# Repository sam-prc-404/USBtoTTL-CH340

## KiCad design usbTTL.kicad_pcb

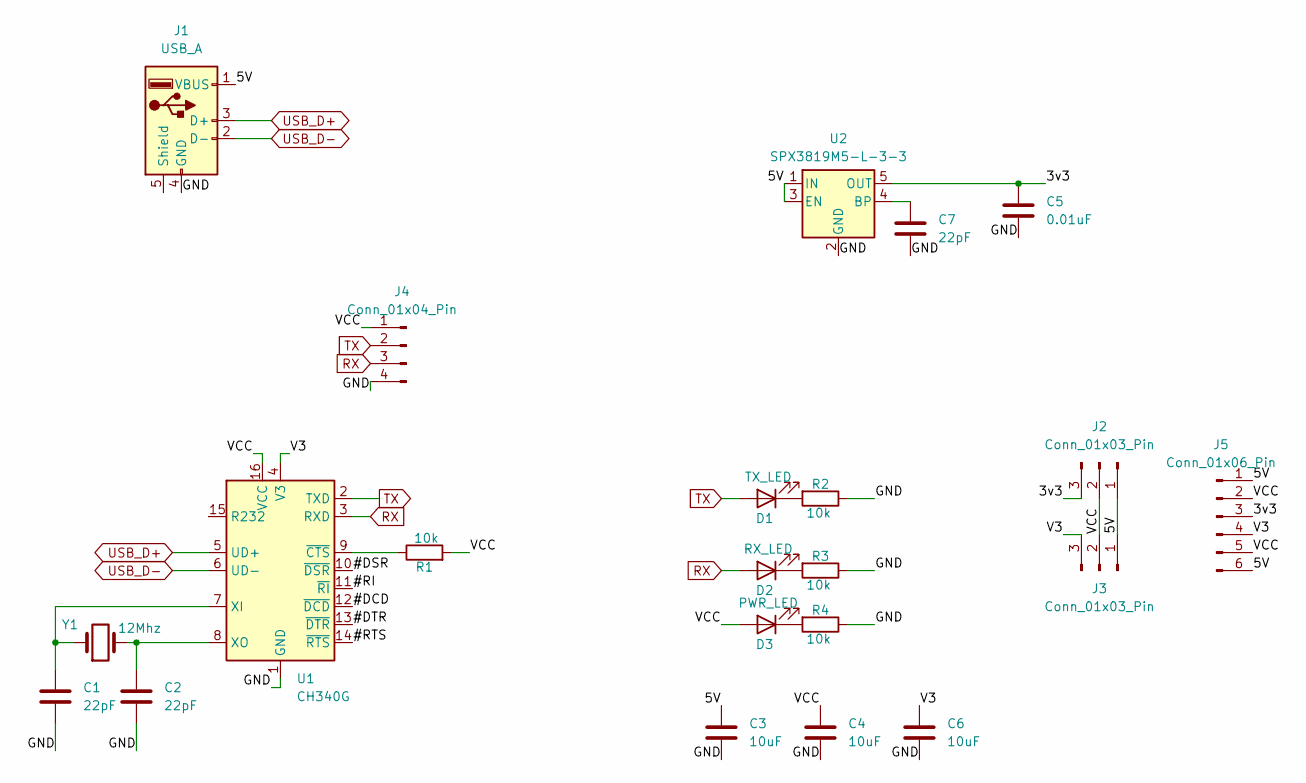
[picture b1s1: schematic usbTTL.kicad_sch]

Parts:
C1, C2, C7: 22pF; C_0805_2012Metric
C3, C4, C6: 10uF; C_0805_2012Metric
C5: 0.01uF; C_0805_2012Metric
D1: TX_LED; LED_0805_2012Metric
D2: RX_LED; LED_0805_2012Metric
D3: PWR_LED; LED_0805_2012Metric
J1: USB_A; USB_A_CNCTech_1001-011-01101_Horizontal
J2, J3: Conn_01x03_Pin; PinSocket_2x03_P2.54mm_Vertical
J4: Conn_01x04_Pin; PinHeader_1x04_P2.54mm_Horizontal
J5: Conn_01x06_Pin; PinHeader_2x03_P2.54mm_Vertical
R1, R2, R3, R4: 10k; R_0805_2012Metric
U1: CH340G; SOIC-16_3.9x9.9mm_P1.27mm
U2: SPX3819M5-L-3-3; SOT-23-5_HandSoldering
Y1: 12Mhz; Crystal_HC18-U_Vertical

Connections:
/3v3: C5.1, J2.3, J5.3, U2.5 (OUT)
/5V: C3.1, J1.1 (VBUS), J2.1, J3.1, J5.1, J5.6, U2.1 (IN), U2.3 (EN)
/#DCD: U1.12 (~DCD)
/#DSR: U1.10 (~DSR)
/#DTR: U1.13 (~DTR)
/#RI: U1.11 (~RI)
/#RTS: U1.14 (~RTS)
/GND: C1.2, C2.2, C3.2, C4.2, C5.2, C6.2, C7.2, J1.4 (GND), J4.4, R2.1, R3.1, R4.1, U1.1 (GND), U2.2 (GND)
/V3: C6.1, J3.3, J5.4, U1.4 (V3)
/VCC: C4.1, D3.2 (A), J2.2, J3.2, J4.1, J5.2, J5.5, R1.2, U1.16 (VCC)
unnamed: D1.1 (K), R2.2
unnamed: D2.1 (K), R3.2
unnamed: D3.1 (K), R4.2
unnamed: C1.1, U1.7 (XI), Y1.1
unnamed: C2.1, U1.8 (XO), Y1.2
unnamed: R1.1, U1.9 (~CTS)
unnamed: C7.1, U2.4 (BP)
RX: D2.2 (A), J4.3, U1.3 (RXD)
TX: D1.2 (A), J4.2, U1.2 (TXD)
USB_D+: J1.3 (D+), U1.5 (UD+)
USB_D-: J1.2 (D-), U1.6 (UD-)

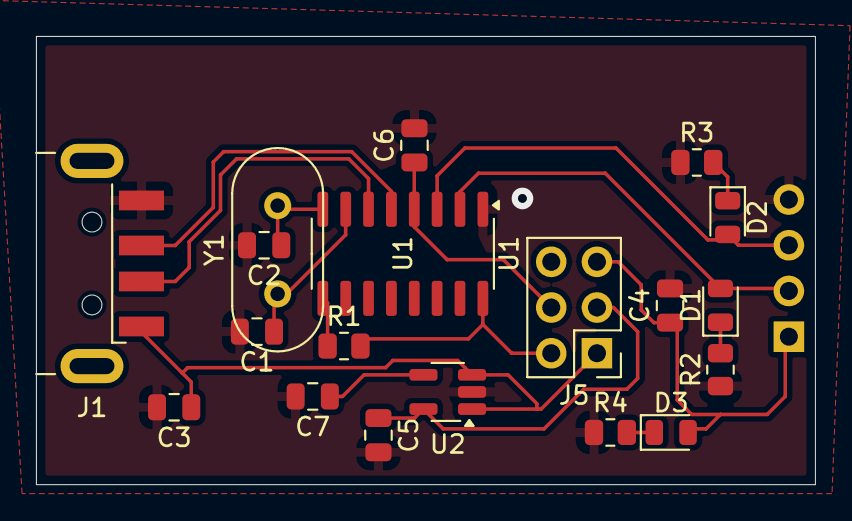
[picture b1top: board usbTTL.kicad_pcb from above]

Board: 2 copper layers, 43.3 x 24.9 mm, 20 parts (1 on the bottom side), 16 nets.

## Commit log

2025-04-29 init
2025-05-05 sync _
2025-05-05 sync 2
